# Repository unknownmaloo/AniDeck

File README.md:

# AniDeck

AniDeck is a custom 5-key macropad featuring a rotary encoder and a 0.91" OLED display, designed specifically for an anime-focused workflow (optimized for the Anikoto platform). It runs KMK firmware on a Seeed Studio XIAO RP2040.

## Features
- **5-key macro layout** with custom shortcuts (Anikoto launcher, resume, play/pause, like, and audio toggle)
- **Rotary Encoder** for system volume control and mute
- **Seeed Studio XIAO RP2040** microcontroller

## CAD Model
The enclosure is a sandwich I designed it in Fusion360, consisting of 2 printed parts:
- Bottom case
- Switch plate

## PCB & Schematic
They both r designed in KiCAD. 

### Schematic

### PCB Layout & 3D Views

## Firmware Overview
- **Framework:** KMK firmware running on CircuitPython.
- **Keymap:** Custom macros and media controls tailored for anime streaming
- **Display:** Static text rendering via Adafruit Displayio libraries

## BOM (Bill of Materials)
Everything needed to build the AniDeck:
- 5× Mechanical switches
- 5× Keycaps
- 1× EC11 Rotary Encoder with push-button
- 1× 0.91" 128×32 OLED display
- 1× Seeed Studio XIAO RP2040
- 1× printed case (Bottom case, Switch plate)
- M3 bolts and heat-set inserts

## AI usage
- **As search engin:** Used to find sources to download different .step files for PCB.
- **Helped in KMK:** It helped me to write KMK firmware for my custom buttons.
- **NOTE:** didn't use it to create auto case not fully dependable on AI.

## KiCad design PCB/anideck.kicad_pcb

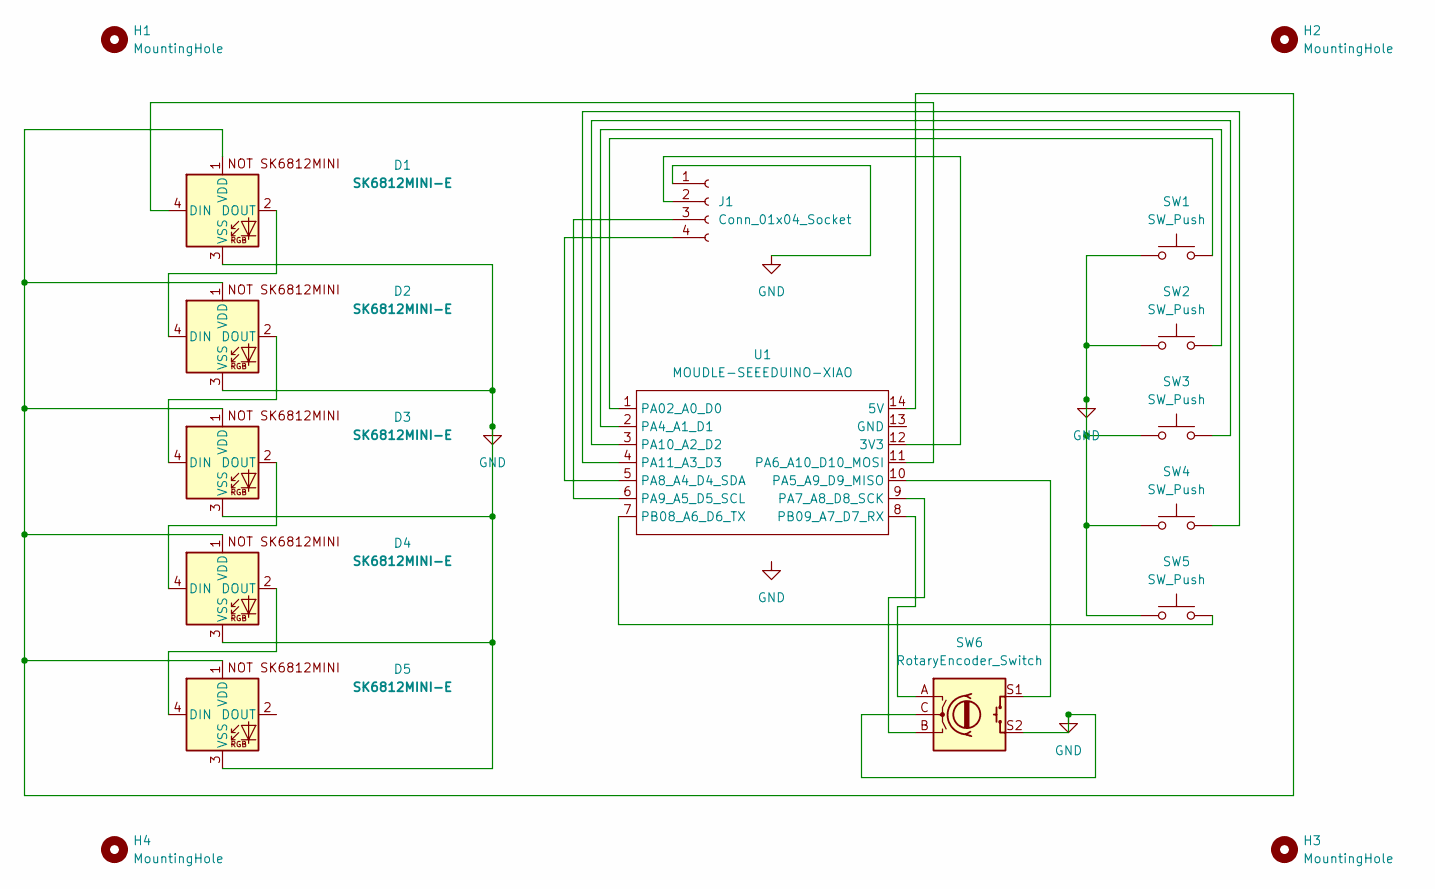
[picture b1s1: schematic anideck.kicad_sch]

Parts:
D1, D2, D3, D4, D5: SK6812MINI-E; SK6812MINI-E_fixed
H1, H2, H3, H4: MountingHole; MountingHole_3.2mm_M3
J1: Conn_01x04_Socket; PinSocket_1x04_P2.54mm_Vertical
SW1, SW2, SW3, SW4, SW5: SW_Push; SW_Cherry_MX_1.00u_PCB
SW6: RotaryEncoder_Switch; RotaryEncoder_Alps_EC11E-Switch_Vertical_H20mm
U1: MOUDLE-SEEEDUINO-XIAO; XIAO-Generic-Hybrid-14P-2.54-21X17.8MM

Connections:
GND: D1.3 (VSS), D2.3 (VSS), D3.3 (VSS), D4.3 (VSS), D5.3 (VSS), J1.1, SW1.1, SW2.1, SW3.1, SW4.1, SW5.1, SW6.C, SW6.S2
unnamed: D1.4 (DIN), U1.11 (PA6_A10_D10_MOSI)
unnamed: D1.2 (DOUT), D2.4 (DIN)
unnamed: D1.1 (VDD), D2.1 (VDD), D3.1 (VDD), D4.1 (VDD), D5.1 (VDD), U1.14 (5V)
unnamed: D2.2 (DOUT), D3.4 (DIN)
unnamed: D3.2 (DOUT), D4.4 (DIN)
unnamed: D4.2 (DOUT), D5.4 (DIN)
unnamed: J1.2, U1.12 (3V3)
unnamed: J1.3, U1.6 (PA9_A5_D5_SCL)
unnamed: J1.4, U1.5 (PA8_A4_D4_SDA)
unnamed: SW1.2, U1.1 (PA02_A0_D0)
unnamed: SW2.2, U1.2 (PA4_A1_D1)
unnamed: SW6.S1, U1.10 (PA5_A9_D9_MISO)
unnamed: SW6.B, U1.9 (PA7_A8_D8_SCK)
unnamed: SW3.2, U1.3 (PA10_A2_D2)
unnamed: SW4.2, U1.4 (PA11_A3_D3)
unnamed: SW5.2, U1.7 (PB08_A6_D6_TX)
unnamed: SW6.A, U1.8 (PB09_A7_D7_RX)

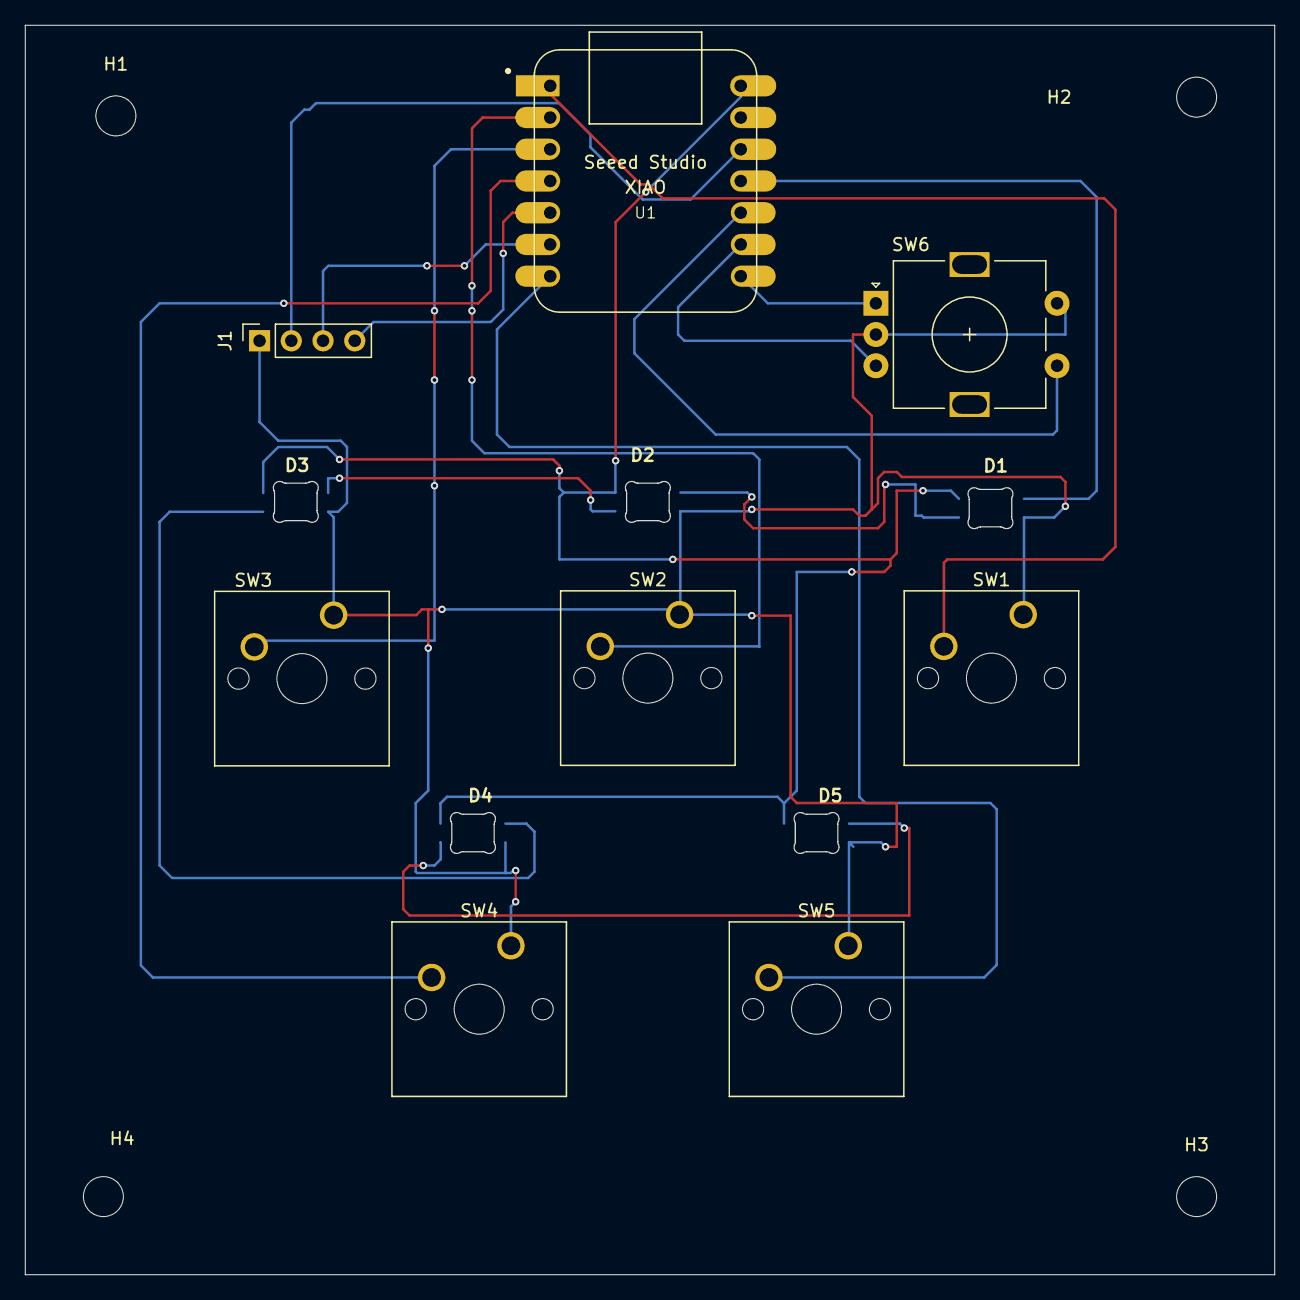
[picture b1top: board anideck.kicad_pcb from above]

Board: 2 copper layers, 100.0 x 100.0 mm, 17 parts (0 on the bottom side), 18 nets.
